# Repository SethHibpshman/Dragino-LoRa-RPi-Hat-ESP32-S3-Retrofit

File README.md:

# Dragino LoRa RPi Hat ESP32 Retrofit

Custom [MeshCore](https://github.com/meshcore-dev/MeshCore) firmware and PCB carrier for running a **Dragino LoRa/GPS HAT** on an **ESP32-S3** instead of the Raspberry Pi it was designed for.

## What this actually is

The Dragino LoRa GPS HAT is built for the Raspberry Pi 40-pin GPIO header. It has no business working with an ESP32-S3 dev board. There's no official pinout for it, no example firmware, and none of the pin numbers on the HAT correspond to anything on an ESP32.

I designed a custom carrier PCB that reroutes the Dragino HAT's SPI, IRQ, and GPS UART lines to an ESP32-S3-DevKitC-1-N16R8, wrote a new MeshCore board target from scratch to drive that hardware, and got it running as three different mesh network node roles: a headless GPS repeater, a Bluetooth companion radio, and a USB-wired companion radio.

Everything here, the PCB, the case, and the firmware, was built to get an off-the-shelf Raspberry Pi accessory running on a completely different microcontroller architecture.

## The hardware

### Custom carrier PCB

The Dragino HAT header doesn't line up with anything on the ESP32-S3, so I designed a board in KiCad that:

- Breaks out both 24-pin rows of the ESP32-S3-DevKitC-1 header
- Routes SPI (SCK/MOSI/MISO), the three LoRa IRQ lines (DIO0/1/2), NSS, and RESET down to the Dragino HAT's Pi-header footprint in the correct positions
- Routes the GPS UART (TX/RX) and I2C (SDA/SCL) separately, since the L80 GPS module and the SSD1306 display need to share the board without colliding with the SPI bus
- Adds a 4-cell battery holder array, a power switch, a buzzer, and a footprint for the OLED and user button, so the whole companion radio build (display, button, buzzer, GPS, LoRa) lives on one board instead of a nest of jumper wires

KiCad project files are in [`/hardware/kicad_project_files`](/hardware/kicad_project_files), and fabrication-ready Gerbers are in [`/hardware/gerbers`](/hardware/gerbers).

### 3D-printed case

Modeled a low-profile tray enclosure to hold the stacked board assembly, sized to the footprint of the carrier PCB with room for the antenna connector and button access.

## What I actually had to figure out

This wasn't a drop-in board support file. Getting MeshCore to run correctly on this combination of parts meant working through a handful of problems that don't show up on boards MeshCore already supports:

**PSRAM pin conflicts.** The N16R8 variant of the ESP32-S3 uses GPIO 35, 36, and 37 internally for OPI PSRAM. Every wiring decision on the carrier board had to route around those three pins, since using them for anything else causes a silent crash on boot.

**No board definition existed for this chip variant.** PlatformIO's stock `esp32-s3-devkitc-1` board JSON doesn't know about the R8 OPI PSRAM, so the board fails with a PSRAM ID error before anything else runs. I wrote a custom `boards/dragino_esp32s3_n16r8.json` with `qio_opi` memory type set explicitly.

**Building a MeshCore target from nothing.** MeshCore expects a `target.h` / `target.cpp` / board class for every supported piece of hardware. There wasn't one for this pairing, so I wrote:
- `DraginoESP32S3Board.h`, a board class that reports the correct IRQ GPIO to the radio driver
- `target.h` / `target.cpp`, wiring up the SX1276 radio driver, the RTC clock with autodetect fallback, the GPS NMEA provider, and the SSD1306/button peripherals conditionally based on which node role is being built

**I2C had to be moved off the default pins by hand.** The ESP32 Arduino core defaults `Wire` to GPIO 21/22, which isn't where the SSD1306 is wired on this board. `Wire.begin(8, 9)` gets called explicitly in `radio_init()`, and the OLED's reset pin (default GPIO 21 in MeshCore) gets overridden to `-1` to avoid landing on the same pin as the display bus.

**Three node roles from one codebase, decided at compile time.** MeshCore can build as a repeater, a BLE companion radio, or (with a small addition I made to the variant's `platformio.ini`) a wired USB companion radio. The BLE-vs-USB choice comes down to whether `BLE_PIN_CODE` is defined at build time: if it is, `main.cpp` compiles in `SerialBLEInterface`; if it isn't, it falls through to plain `ArduinoSerialInterface` and the companion protocol runs over native USB serial instead. Same firmware logic, same wiring, different transport, chosen by which PlatformIO environment you flash.

## Node roles

| Role | Connectivity | Use case |
|---|---|---|
| **Repeater** | None (headless) | Deploy high, leave powered, extends mesh range, beacons GPS |
| **Companion Radio (BLE)** | Bluetooth to phone | Carry with you, OLED + button + buzzer, pairs with the MeshCore app |
| **Companion Radio (USB)** | Wired serial | Same features as BLE, plugs into a PC or SBC instead of pairing |

All three are built from the same variant and the same wiring; the only thing that changes is which PlatformIO environment gets flashed.

## Firmware

The firmware is a set of files that drop into a clone of [MeshCore](https://github.com/meshcore-dev/MeshCore). Each folder in [`/firmware`](/firmware) mirrors the MeshCore directory layout, so its contents copy straight into the root of the clone. There are two versions:

| Folder | Hardware | Node roles |
|---|---|---|
| [`full_node`](/firmware/full_node) | Carrier PCB: LoRa, GPS, SSD1306 OLED, button, and buzzer | Repeater, Companion (BLE), Companion (USB) |
| [`lora_only`](/firmware/lora_only) | Dragino HAT jumper-wired to the ESP32-S3, LoRa radio only | Repeater, Companion (BLE) |

```
firmware/full_node/
├── boards/
│   └── dragino_esp32s3_n16r8.json      # Custom board definition (OPI PSRAM fix)
├── examples/
│   └── companion_radio/
│       └── main.cpp                    # Modified MeshCore companion entry point (BLE or USB)
└── variants/
    └── dragino_esp32s3/
        ├── DraginoESP32S3Board.h       # Board class (LoRa IRQ GPIO)
        ├── target.h                    # Hardware declarations
        ├── target.cpp                  # Radio, GPS, I2C, display, and button setup
        └── platformio.ini              # Build environments (repeater, BLE, USB)
```

`lora_only` has the same layout without `examples/`. `main.cpp` and the variant structure are adapted from MeshCore, which is MIT licensed.

## Building it

Please see the [setup guide](../../wiki) in the wiki for parts, wiring, firmware setup, flashing, and troubleshooting.

---

## Author

**Seth Hibpshman**  
Student of Electrical Engineering, Eastern Washington University

## AI Disclosure
_AI (LLM) tools were used for quality assurance review of the firmware and in the drafting and editing of this README and wiki documentation; all code was written by hand._

## License

[GNU General Public License v3.0](LICENSE)

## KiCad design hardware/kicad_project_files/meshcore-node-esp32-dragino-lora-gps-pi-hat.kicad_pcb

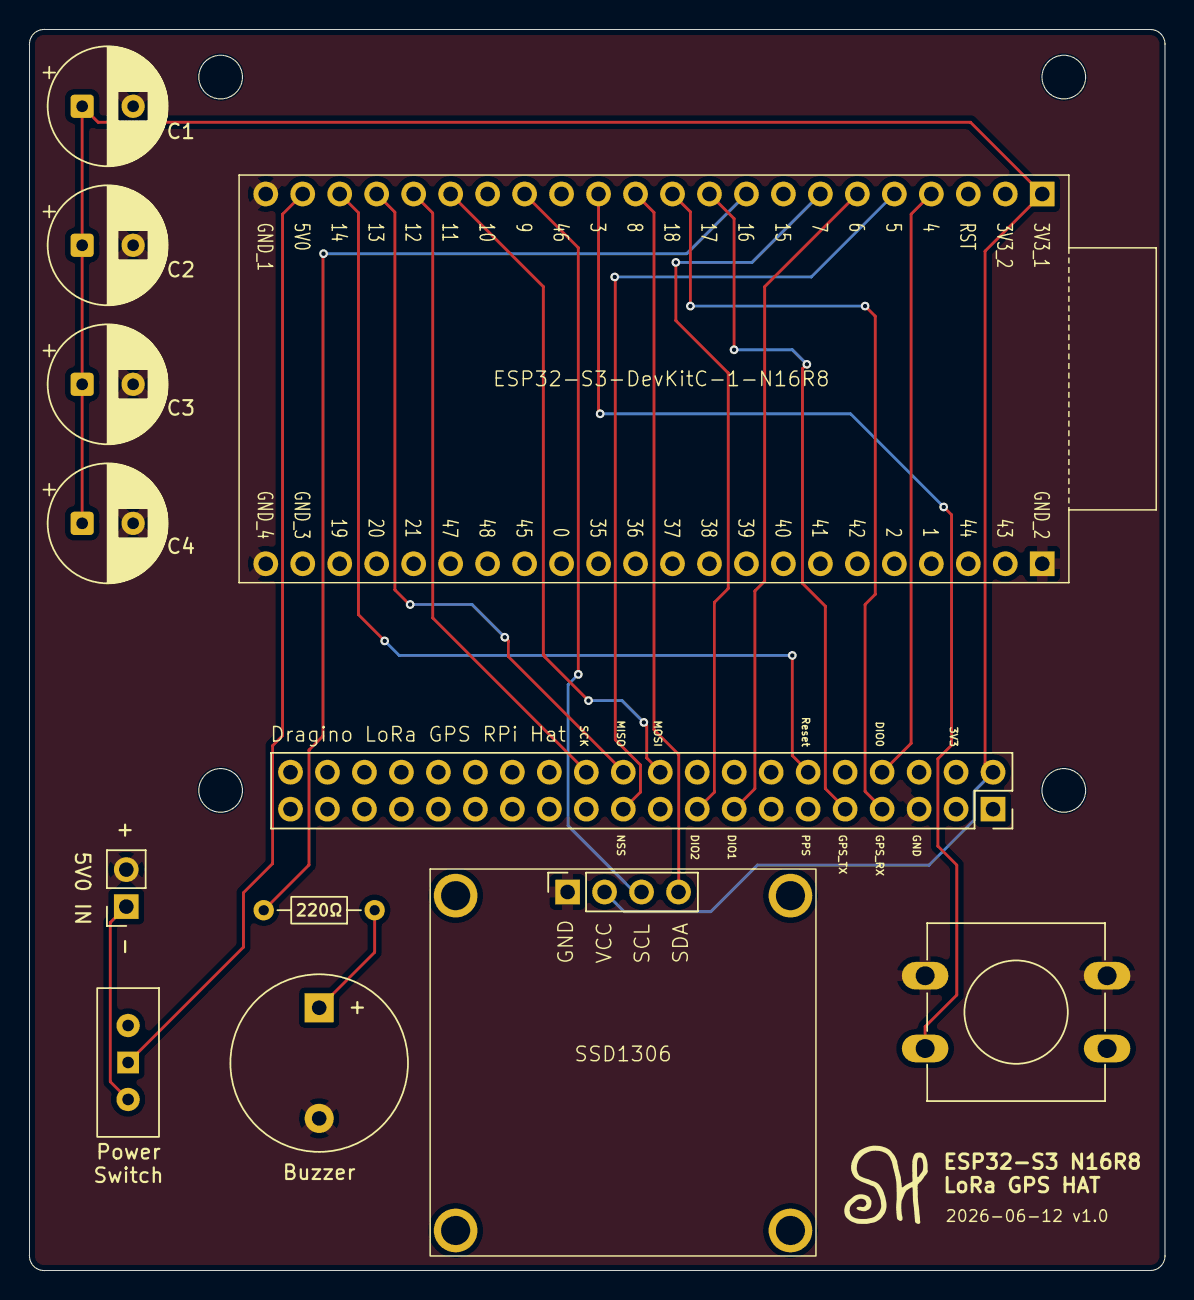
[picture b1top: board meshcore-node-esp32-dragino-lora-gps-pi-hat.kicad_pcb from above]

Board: 2 copper layers, 78.0 x 85.2 mm, 12 parts (0 on the bottom side), 19 nets.

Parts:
Buzzer: Buzzer_12x9.5RM7.6
C1, C2, C3, C4: C_Polarized; CP_Radial_D8.0mm_P3.50mm
ESP32-S3-DevKitC-1-N16R8: ESP32-S3 Mount
H1: Dragino_LoRa_GPS_RPi_Hat
PWR_SW1: SW_Wuerth_450301014042; SW_Slide-03_Wuerth-WS-SLTV_10x2.5x6.4_P2.54mm
R1: R_US; R_Axial_DIN0204_L3.6mm_D1.6mm_P7.62mm_Horizontal
SSD1306: ssd1306 - mounting holes
SW1: SW_Push; SW_PUSH-12mm
Z3: 5v Supply; PinSocket_1x02_P2.54mm_Vertical

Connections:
+3V3: C1.1, C2.1, C3.1, C4.1, ESP32-S3-DevKitC-1-N16R8.3V3_1 (3V3), H1.2 (3.3v), SSD1306.2 (VCC)
+5V: ESP32-S3-DevKitC-1-N16R8.5V0, PWR_SW1.1 (B)
/GPIO3: ESP32-S3-DevKitC-1-N16R8.3 (GPIO3), SW1.2
/GPIO4: ESP32-S3-DevKitC-1-N16R8.4 (GPIO4), H1.8 (LoRa_DIO0)
/GPIO5: ESP32-S3-DevKitC-1-N16R8.5 (GPIO5), H1.21 (LoRa_NSS)
/GPIO6: ESP32-S3-DevKitC-1-N16R8.6 (GPIO6), H1.15 (LoRa_DIO1)
/GPIO7: ESP32-S3-DevKitC-1-N16R8.7 (GPIO7), H1.17 (LoRa_DIO2)
/GPIO8: ESP32-S3-DevKitC-1-N16R8.8 (GPIO8), SSD1306.4 (SDA)
/GPIO9: ESP32-S3-DevKitC-1-N16R8.9 (GPIO9), SSD1306.3 (SCL)
/GPIO11: ESP32-S3-DevKitC-1-N16R8.11 (GPIO11), H1.20 (LoRa_MOSI)
/GPIO12: ESP32-S3-DevKitC-1-N16R8.12 (GPIO12), H1.24 (LoRa_SCK)
/GPIO13: ESP32-S3-DevKitC-1-N16R8.13 (GPIO13), H1.22 (LoRa_MISO)
/GPIO14: ESP32-S3-DevKitC-1-N16R8.14 (GPIO14), H1.12 (LoRa_Reset)
/GPIO16: ESP32-S3-DevKitC-1-N16R8.16 (GPIO16), R1.2
/GPIO17: ESP32-S3-DevKitC-1-N16R8.17 (GPIO17), H1.9 (GPS_TX)
/GPIO18: ESP32-S3-DevKitC-1-N16R8.18 (GPIO18), H1.7 (GPS_RX)
GND: Buzzer.2 (-), C1.2, C2.2, C3.2, C4.2, ESP32-S3-DevKitC-1-N16R8.GND_1 (GND), ESP32-S3-DevKitC-1-N16R8.GND_2 (GND), ESP32-S3-DevKitC-1-N16R8.GND_4 (GND), H1.5 (GND), SSD1306.1 (GND), SW1.1, Z3.2 (GND)
unnamed: Buzzer.1 (+), R1.1
unnamed: PWR_SW1.3 (A), Z3.1 (VCC)
